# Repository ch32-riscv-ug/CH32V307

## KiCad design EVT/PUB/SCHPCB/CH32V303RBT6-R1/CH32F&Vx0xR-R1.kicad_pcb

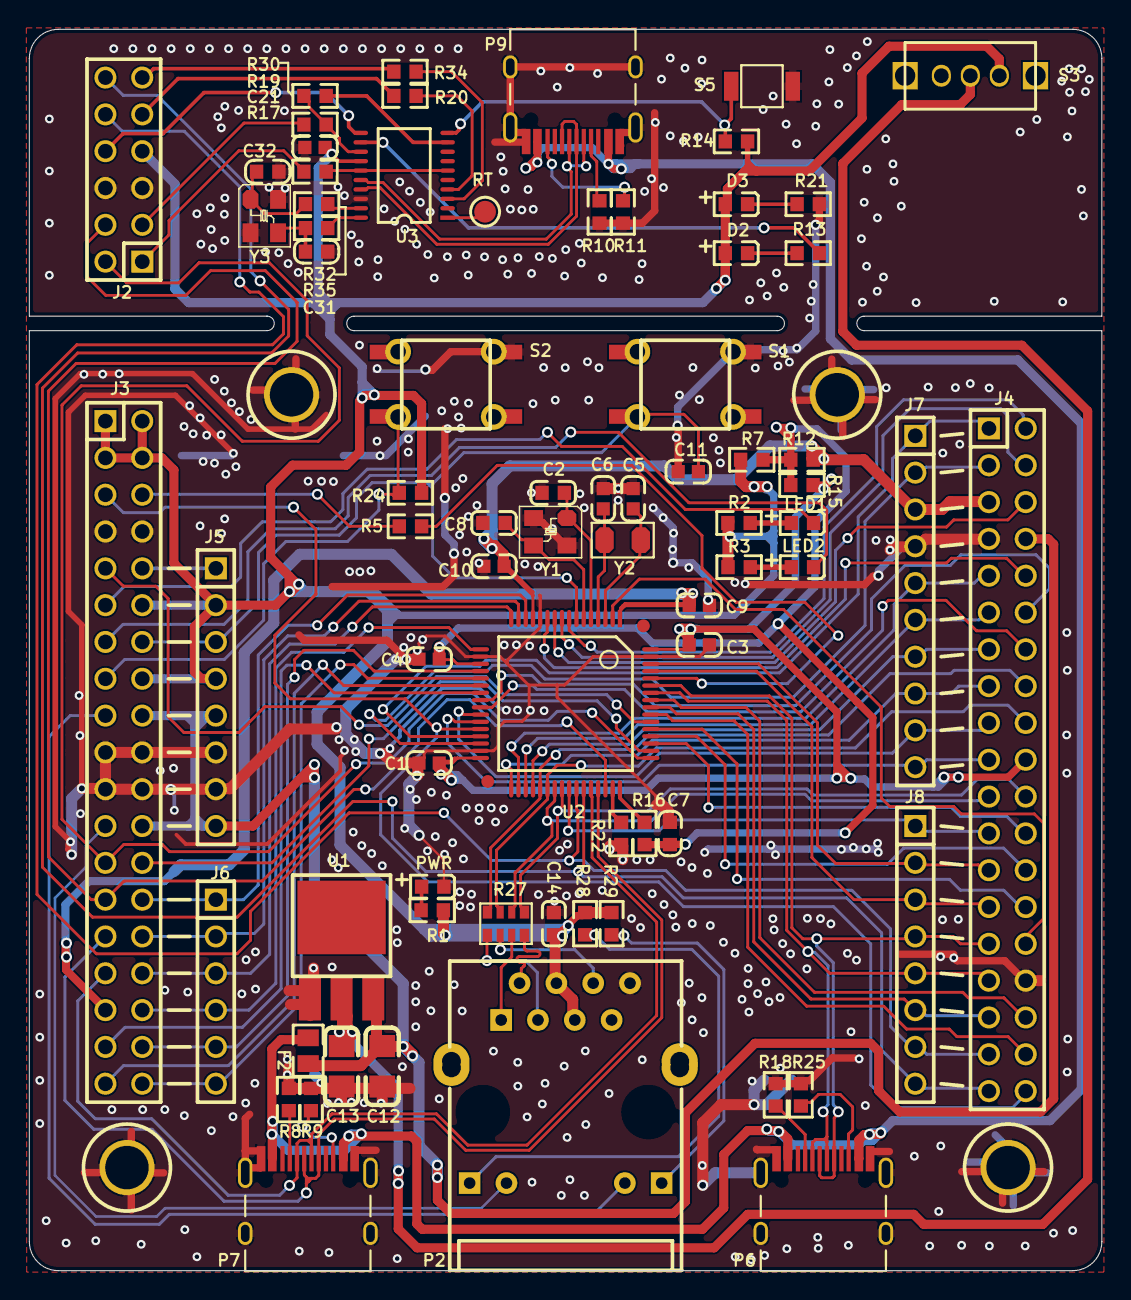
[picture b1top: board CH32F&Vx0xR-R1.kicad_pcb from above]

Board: 2 copper layers, 74.0 x 85.6 mm, 74 parts (0 on the bottom side), 107 nets.

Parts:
C1, C3, C4, C7, C9, C10, C11, C21: 0.1uF; 0603_C
C2, C8: 22pF; 0603_C
C5, C6: 12pF; 0603_C
C12, C13: 10uF; 3216_C
C14: 1uF; 0603_C
C31, C32: NC(22pF); 0603_C
D2: BLUE; 0603+
D3: RED; 0603+
F2: 500mA; 0805
J2: Header 6X2; IDC12-2.54mm
J3, J4: Header 19X2; IDC38-2.54mm
J5, J8: Header 8; SIP8-2.54mm
J6: Header 6; SIP6-2.54MM
J7: Header 10; SIP10-2.54mm
LED1: LED1 blue; 0603+
LED2: LED2 blue; 0603+
P2: HR911105A
P6, P9: TYPE-C; TYPE-C-Receptacle-2.0
P7: USBFS; TYPE-C-Receptacle-2.0
PWR: POWER red; 0603+
R1, R2, R3, R13, R21, R28, R29, R30: 1K; 0603
R5, R14, R24: 10K; 0603
R7, R12, R15: 0Ω; 0603
R8, R9, R10, R11, R18, R25: NC(5.1K); 0603
R16, R22: 0; 0603
R17, R19: 100; 0603
R20, R34: 270; 0603
R27: 0Ω; 8P4R-0603
R32, R35: NC(0R); 0603
RT: Testpoint; TESTPOINT1
S1: RESET; KEYX
S2: USER; KEYX
S3: SW; SW1
S5: KEY; 贴片按键
U1: 1117-3.3V; SOT-223
U2: CH32V307R; LQFP64M_10X10
U3: CH32V305F; TSSOP20
Y1: 8MHz; XT3225
Y2: 32.768k; FC-135
Y3: NC(12M); XT3225

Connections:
5V_in: F2.1, P6.A4, P6.B4, P7.A4, P7.B4, P9.A4, P9.B4
+5V: C12.1, F2.2, J3.18, J3.24, J4.8, J5.5, J5.8, U1.3
BOOT0: R5.2, U2.60
BOOT1: J3.5, J4.38, U2.28
CLK: J2.2, J3.25, U2.49
CLK0: J2.1, R17.1
DIO: J2.4, J3.27, U2.46
DIO0: J2.3, R19.1
D_SWCLK: R17.2, U3.6, U3.15
D_SWDIO: R19.2, R30.1, U3.13
ELED1: J3.23, P2.10
ELED2: J3.17, P2.11
ERXN: J4.18, R27.3, U2.38
ERXN1: P2.6, R27.6
ERXP: J4.16, R27.4, U2.37
ERXP1: P2.3, R27.5
ETXN: J4.22, R27.1, U2.40
ETXN1: P2.2, R27.8
ETXP: J4.21, R27.2, U2.39
ETXP1: P2.1, R27.7
GND: C1.1, C2.1, C3.1, C4.1, C5.2, C6.2, C7.1, C8.1, C9.2, C10.2, C11.1, C12.2, C13.2, C14.1, C21.2, C31.1, C32.1, J2.5, J2.6, J3.7, J3.8, J3.19, J3.20, J3.21, J3.22, J4.7, J4.32, J5.6, J5.7, J7.4, P2.8, P6.0, P6.A1, P6.B1, P7.0, P7.A1, P7.B1, P9.0, P9.A1, P9.B1, PWR.2, R8.1, R9.1, R10.2, R11.2, R18.1, R21.1, R22.1, R25.1, S1.3, S2.3, S5.2, U1.1, U2.12, U2.18, U2.31, U2.63, U3.18, Y1.2, Y1.4, Y3.2, Y3.4
IAP: R14.1, S5.1, U3.10
KEY: J3.15, R24.1, S2.1
LED1: J3.11, LED1.2
LED2: J3.13, LED2.2
LED_CON: R13.1, U3.12
NRST: C11.2, J3.14, J5.3, S1.1, U2.7
NetC13_1: C13.1, S3.1, U1.2
NetD2_2: D2.2, R13.2
NetD3_2: D3.2, R21.2
NetJ3_6: J3.6, R5.1
NetJ3_10: J3.10, J5.1
NetLED1_1: LED1.1, R2.2
NetLED2_1: LED2.1, R3.2
NetP2_9: P2.9, R28.2
NetP2_12: P2.12, R29.2
NetP6_A5: P6.A5, R18.2
NetP6_B5: P6.B5, R25.2
NetP7_A5: P7.A5, R8.2
NetP7_B5: P7.B5, R9.2
NetP9_A5: P9.A5, R10.1
NetP9_B5: P9.B5, R11.1
NetPWR_1: PWR.1, R1.1
NetR16_2: R16.2, U2.48
NetR22_2: R22.2, U2.47
OSC_IN: C32.2, R32.2, Y3.1
OSC_OUT: C31.2, R35.2, Y3.3
PA0: J3.28, J6.1, U2.14
PA1: J3.30, J6.2, U2.15
PA2: J3.32, J6.3, U2.16
PA3: J3.34, J6.4, U2.17
PA4: J3.36, J6.5, U2.20
PA5: J3.38, J6.6, U2.21
PA6: J3.37, U2.22
PA7: J3.35, U2.23
PA8: J4.23, J8.1, U2.41
PA9: J2.10, J4.35, J8.7, U2.42
PA10: J2.12, J4.37, J8.8, U2.43
PA11: J3.31, P7.A7, P7.B7, U2.44
PA12: J3.29, P7.A6, P7.B6, U2.45
PA15: J3.26, U2.50
PB0: J4.17, J7.9, U2.26
PB1: J4.19, J7.10, U2.27
PB3: J4.36, U2.55
PB4: J4.33, J8.6, U2.56
PB5: J4.34, U2.57
PB6: J4.31, J8.5, P6.A7, P6.B7, U2.58
PB7: J4.29, J8.4, P6.A6, P6.B6, U2.59
PB8: J4.27, J8.3, U2.61
PB9: J4.25, J8.2, U2.62
PB10: J4.1, J7.1, U2.29
PB11: J4.3, J7.2, U2.30
PB12: J4.15, J7.8, U2.33
PB13: J4.9, J7.5, U2.34
PB14: J4.11, J7.6, U2.35
PB15: J4.13, J7.7, U2.36
PC0: J4.2, U2.8
PC1: J4.4, U2.9
PC2: J4.6, U2.10
PC3: J4.10, U2.11
PC4: J4.12, U2.24
PC5: J4.14, U2.25
PC6_305: R30.2, U3.9
PC10: J4.24, U2.51
PC11: J4.26, U2.52
PC12: J4.28, U2.53
PC13: J4.30, U2.2
PC14: C5.1, U2.3, Y2.1
PC15: C6.1, U2.4, Y2.2
PD0: C2.2, U2.5, Y1.1
PD0_305: R32.1, U3.19
PD1: C8.2, U2.6, Y1.3
PD1_305: R35.1, U3.20
PD2: J3.9, U2.54
RST0: J2.8, U3.11
RT: RT.1, U3.1
RX_OUT: J2.9, R20.1
TX_OUT: J2.11, R34.1
UART3_RX: R20.2, U3.4
UART3_TX: R34.2, U3.3
USB_N: P9.A7, P9.B7, U3.16
USB_P: P9.A6, P9.B6, U3.17
VBAT: C9.1, J3.33, U2.1
VCC: C14.2, C21.1, D2.1, D3.1, J2.7, J3.1, J3.2, J3.3, J3.4, J3.12, J3.16, J5.2, J5.4, P2.4, P2.5, R1.2, R2.1, R3.1, R7.1, R14.2, R24.2, R28.1, R29.1, S3.3, U3.14
VDD: C4.2, C7.2, R7.2, R12.2, R15.2, R16.1, U2.19
VDDA: C10.1, J4.5, J7.3, R12.1, U2.13
VIO: C1.2, C3.2, J4.20, R15.1, U2.32, U2.64
